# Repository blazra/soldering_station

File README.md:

Deprecated in favor of this: https://github.com/Jan--Henrik/Otter-Iron-PRO

# JBC T210 Soldering Iron Controller

This is my first project using embedded Rust. :hugs:

Schematic: [hardware/control_board/rev2/soldering_station.pdf](hardware/control_board/rev2/soldering_station.pdf)

- Rev. 2 of the control board works fine :tada:, but I need to think of a better mechanical solution for the whole station.

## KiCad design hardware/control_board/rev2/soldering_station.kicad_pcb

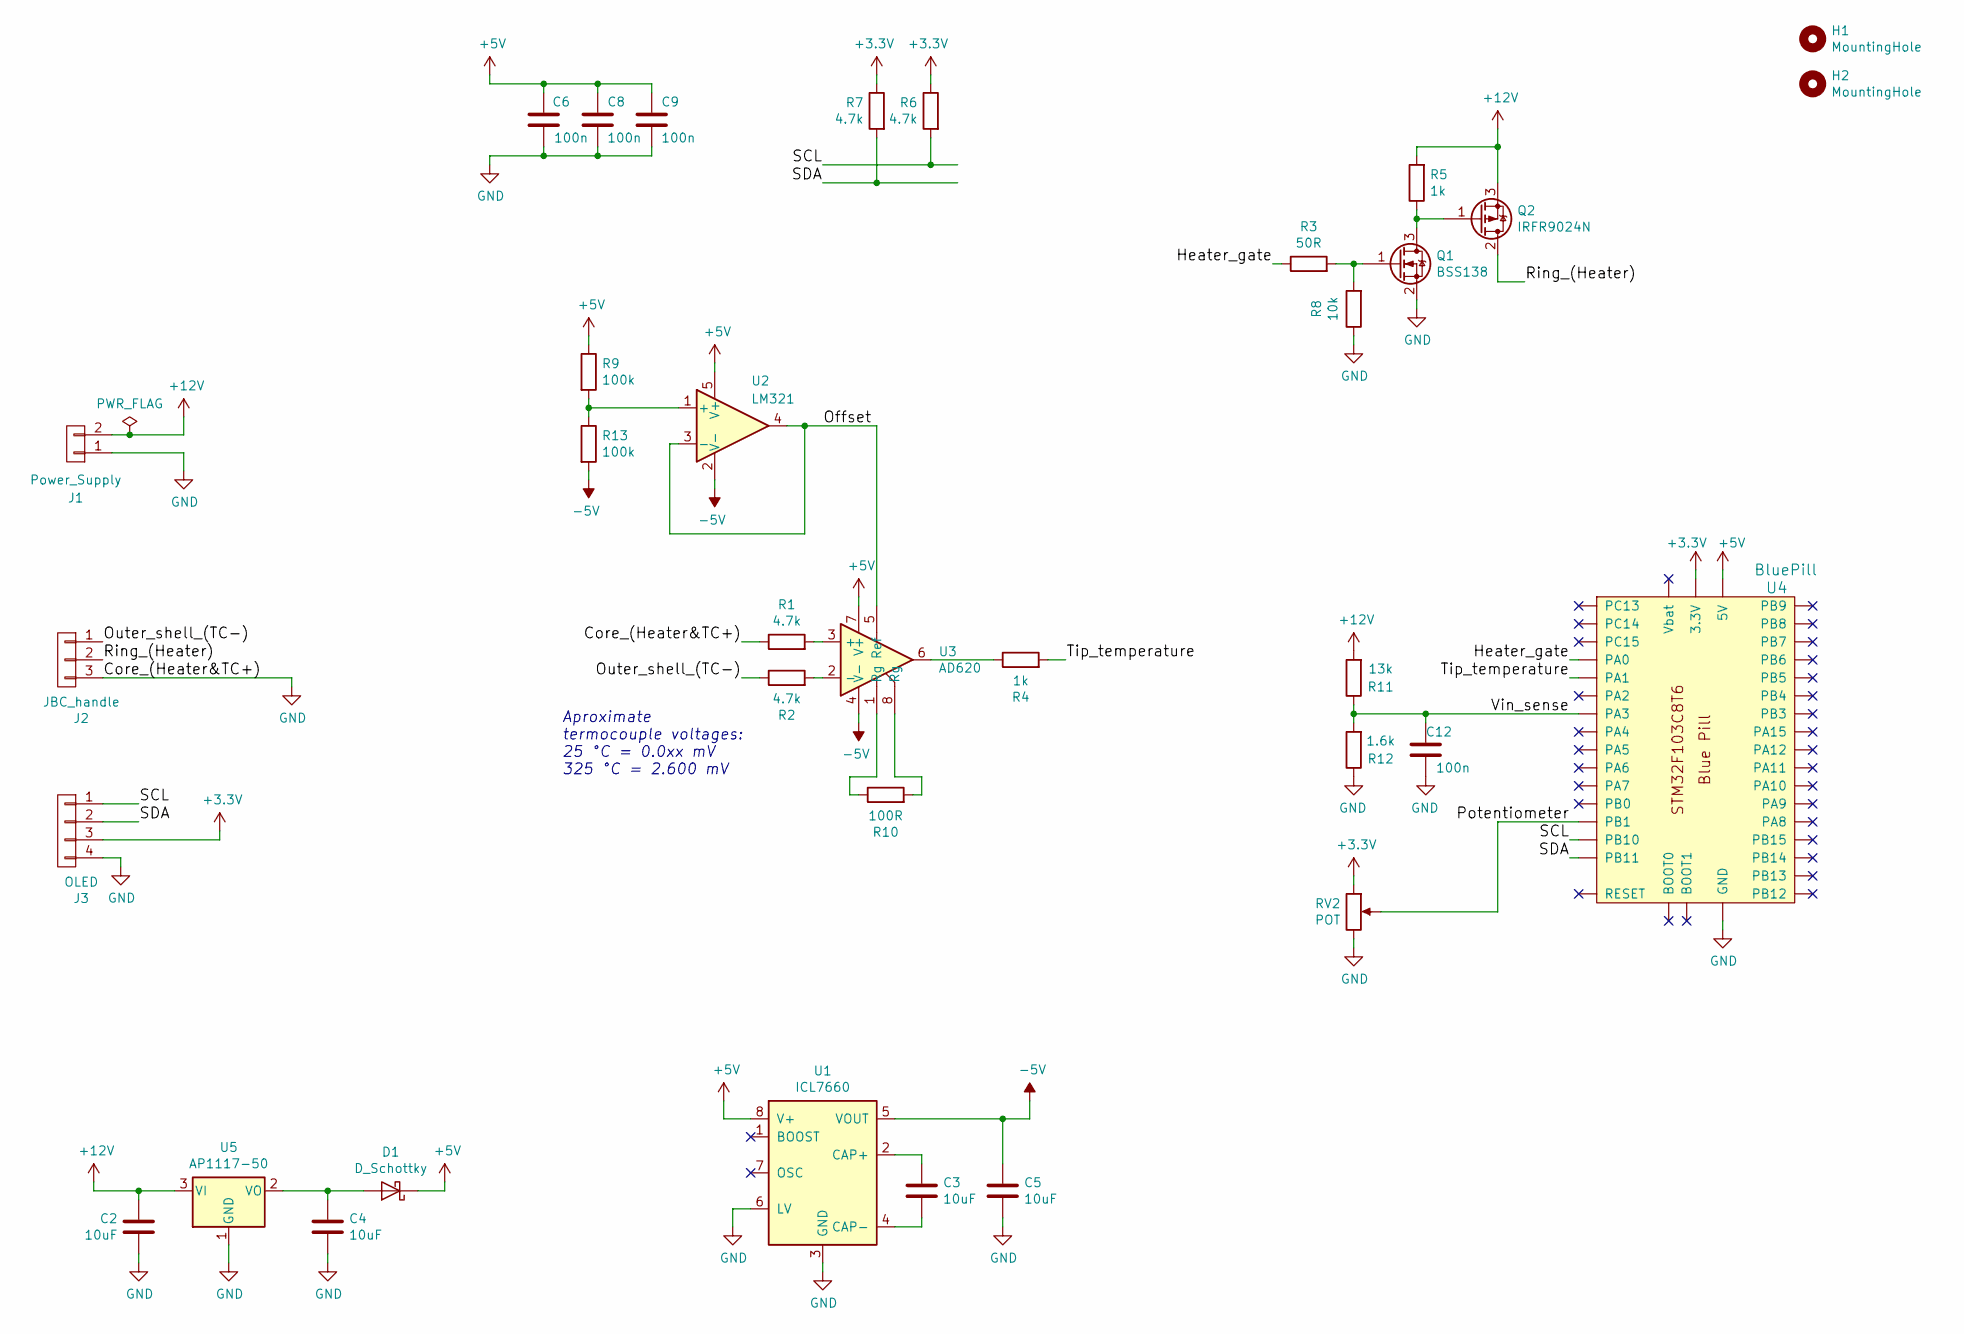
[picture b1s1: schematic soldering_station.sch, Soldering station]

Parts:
C2, C3, C4, C5: 10uF; C_0805_2012Metric
C6, C8, C9, C12: 100n; C_0805_2012Metric
D1: D_Schottky; D_MiniMELF
H1, H2: MountingHole; MountingHole_2.2mm_M2
J1: Power_Supply; Molex_KK-254_AE-6410-02A_1x02_P2.54mm_Vertical
J2: JBC_handle; Molex_KK-254_AE-6410-03A_1x03_P2.54mm_Vertical
J3: OLED; PinHeader_1x04_P2.54mm_Vertical
Q1: BSS138; SOT-23
Q2: IRFR9024N; TO-252-3_TabPin2
R1, R2, R6, R7: 4.7k; R_0805_2012Metric
R3: 50R; R_0805_2012Metric
R4, R5: 1k; R_0805_2012Metric
R8: 10k; R_0805_2012Metric
R9, R13: 100k; R_0805_2012Metric
R10: 100R; R_0805_2012Metric
R11: 13k; R_0805_2012Metric
R12: 1.6k; R_0805_2012Metric
RV2: POT; PinHeader_1x03_P2.54mm_Vertical
U1: ICL7660; SOIC-8_3.9x4.9mm_P1.27mm
U2: LM321; SOT-23-5
U3: AD620; SOIC-8_3.9x4.9mm_P1.27mm
U4: BluePill
U5: AP1117-50; SOT-223-3_TabPin2

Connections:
+3V3: J3.3, R6.1, R7.1, RV2.1, U4.3V3 (3.3V)
+5V: C6.1, C8.1, C9.1, D1.1 (K), R9.1, U1.8 (V+), U2.5 (V+), U3.7 (V+), U4.5V
+12V: C2.1, J1.2, Q2.3 (S), R5.2, R11.2, U5.3 (VI)
-5V: C5.1, R13.2, U1.5 (VOUT), U2.2 (V-), U3.4 (V-)
/Heater_gate: R3.1, U4.PA0
/Outer_shell_(TC-): J2.1, R2.1
/Potentiometer: RV2.2, U4.PB1
/Ring_(Heater): J2.2, Q2.2 (D)
/SCL: J3.1, R6.2, U4.PB10
/SDA: J3.2, R7.2, U4.PB11
/Tip_temperature: R4.2, U4.PA1
/Vin_sense: C12.1, R11.1, R12.2, U4.PA3
unnamed: C3.1, U1.2 (CAP+)
unnamed: C3.2, U1.4 (CAP-)
unnamed: C4.1, D1.2 (A), U5.2 (VO)
unnamed: Q1.1 (G), R3.2, R8.2
unnamed: Q1.3 (D), Q2.1 (G), R5.1
unnamed: R1.2, U3.3 (+)
unnamed: R2.2, U3.2 (-)
unnamed: R4.1, U3.6
unnamed: R10.1, U3.1 (Rg)
unnamed: R10.2, U3.8 (Rg)
unnamed: R9.2, R13.1, U2.1 (+)
unnamed: U2.3 (-), U2.4, U3.5 (Ref)

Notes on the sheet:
Aproximate termocouple voltages: 25 °C = 0.0xx mV 325 °C = 2.600 mV

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
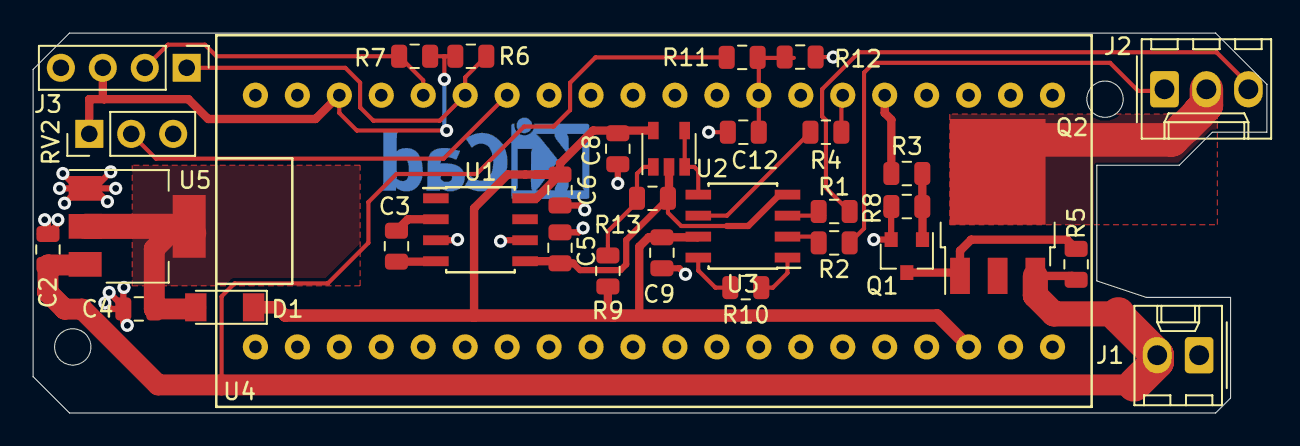
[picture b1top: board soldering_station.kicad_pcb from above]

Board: 2 copper layers, 74.7 x 23.0 mm, 35 parts (0 on the bottom side), 25 nets.

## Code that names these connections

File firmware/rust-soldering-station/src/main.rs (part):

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use stm32f1xx_hal::{
    prelude::*,
    pac,
    gpio::{gpioa::PA0, gpioc::PC13, gpiob::PB10, gpiob::PB11, Output, PushPull, OpenDrain, Alternate},
    device::I2C2,
    device::TIM2,
    device::ADC1,
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
use embedded_hal::digital::v2::OutputPin;

struct MyChannels(PA0<Alternate<PushPull>>);

impl Pins<TIM2> for MyChannels
{
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
/////////////////////////////////////////
// Pins in HW revision 2:              //
// Heater gate:     PA0                //
// Tip temperature: PA1, ADC channel 1 //
// Vin sense:       PA3, ADC channel 3 //
// Potentiometer:   PB1, ADC channel 9 //
// Chip temperature: ADC channel 16    //
// SCL:             PB10               //
// SDA:             PB11               //
/////////////////////////////////////////

#[rtfm::app(device = stm32f1xx_hal::pac)]
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        ssd1306::interface::I2cInterface<
            BlockingI2c<
                I2C2,(
                    PB10<Alternate<OpenDrain>>,
                    PB11<Alternate<OpenDrain>>
                )
            >
        >
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
    static mut led_on: bool = true;
    static mut chip_temperature: i16 = 0;
    static mut tip_temperature: i16 = 0;
    static mut set_temperature: u16 = 0;
    static mut duty: u16 = 0;

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        let mut gpiob = peripherals.GPIOB.split(&mut rcc.apb2);
        let mut gpioc = peripherals.GPIOC.split(&mut rcc.apb2);

        let heater_gate = gpioa.pa0.into_alternate_push_pull(&mut gpioa.crl);

        let mut pwm_temp = peripherals.TIM2.pwm(
            MyChannels(heater_gate),
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        pwm_temp.set_duty(0);
        pwm_temp.enable();

        let scl = gpiob.pb10.into_alternate_open_drain(&mut gpiob.crh);
        let sda = gpiob.pb11.into_alternate_open_drain(&mut gpiob.crh);

        let i2c = BlockingI2c::i2c2(
            peripherals.I2C2,
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
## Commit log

2019-06-14 Create LICENSE
2019-06-14 Rename LICENSE to LICENSE-0BSD.txt
2019-06-14 Add license to Cargo manifest
2019-06-14 Add rendered soldering station image
2019-06-14 Fix typo in readme
2019-06-15 Add Cargo.lock file
2019-08-04 Ignore fp-info-cache; Keep *-cache.lib
2019-09-05 Port firmware to new versions of rtfm and embedded_graphics
2019-09-30 Setup Github Actions
2019-09-30 Add .cargo/config
2019-09-30 rust.yml: fix typo
2020-05-18 Deprecate the project
